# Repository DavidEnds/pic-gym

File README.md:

# pic-gym
A basic trainer for the PIC16F84A

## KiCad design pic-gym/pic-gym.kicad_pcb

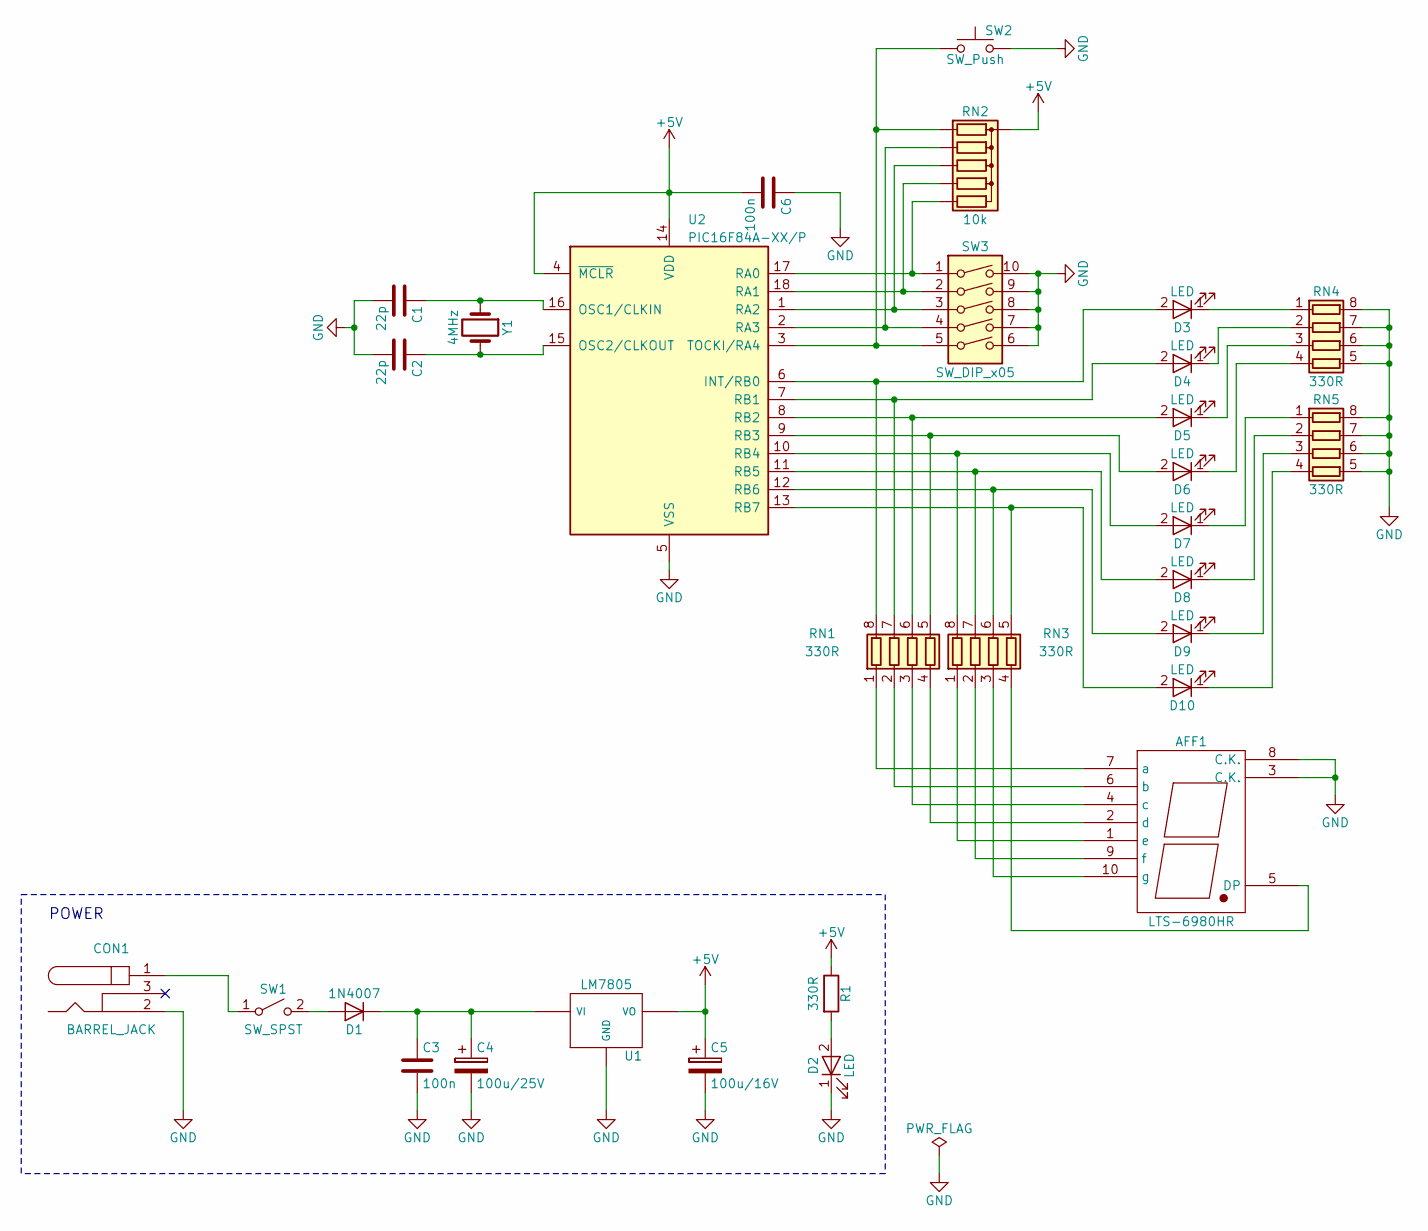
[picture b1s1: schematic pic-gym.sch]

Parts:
AFF1: LTS-6980HR; 7SegmentLED_LTS6760_LTS6780
C1, C2: 22p; C_0805_HandSoldering
C3, C6: 100n; C_0805_HandSoldering
C4: 100u/25V; C_Radial_D5_L11_P2
C5: 100u/16V; C_Radial_D5_L11_P2
CON1: BARREL_JACK; JACK_ALIM
D1: 1N4007; Diode_DO-35_SOD27_Horizontal_RM10
D2, D3, D4, D5, D6, D7, D8, D9, D10: LED; LED-3MM
R1: 330R; Resistor_Horizontal_RM10mm
RN1, RN3, RN4, RN5: 330R; R_Array_Concave_4x0603
RN2: 10k; Resistor_Array_SIP6
SW1: SW_SPST; SW_DIP_x1_Slide
SW2: SW_Push; SW_PUSH_6mm
SW3: SW_DIP_x05; SW_DIP_x5_Slide
U1: LM7805; TO-220_Neutral123_Vertical
U2: PIC16F84A-XX/P; DIP-18_W7.62mm_LongPads
Y1: 4MHz; HC-49V

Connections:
+5V: C5.1, C6.2, R1.1, RN2.1 (common), U1.3 (VO), U2.4 (~MCLR~), U2.14 (VDD)
GND: AFF1.3 (C.K.), AFF1.8 (C.K.), C1.2, C2.2, C3.2, C4.2, C5.2, C6.1, CON1.2, D2.1 (K), RN4.5 (R4.2), RN4.6 (R3.2), RN4.7 (R2.2), RN4.8 (R1.2), RN5.5 (R4.2), RN5.6 (R3.2), RN5.7 (R2.2), RN5.8 (R1.2), SW2.2, SW3.6, SW3.7, SW3.8, SW3.9, SW3.10, U1.2 (GND), U2.5 (VSS)
unnamed: AFF1.1 (e), RN3.1 (R1.1)
unnamed: AFF1.2 (d), RN1.4 (R4.1)
unnamed: AFF1.4 (c), RN1.3 (R3.1)
unnamed: AFF1.5 (DP), RN3.4 (R4.1)
unnamed: AFF1.6 (b), RN1.2 (R2.1)
unnamed: AFF1.7 (a), RN1.1 (R1.1)
unnamed: AFF1.9 (f), RN3.2 (R2.1)
unnamed: AFF1.10 (g), RN3.3 (R3.1)
unnamed: C1.1, U2.16 (OSC1/CLKIN), Y1.1
unnamed: C2.1, U2.15 (OSC2/CLKOUT), Y1.2
unnamed: C3.1, C4.1, D1.1 (K), U1.1 (VI)
unnamed: CON1.1, SW1.1 (A)
unnamed: D1.2 (A), SW1.2 (B)
unnamed: D2.2 (A), R1.2
unnamed: D3.1 (K), RN4.1 (R1.1)
unnamed: D3.2 (A), RN1.8 (R1.2), U2.6 (INT/RB0)
unnamed: D4.1 (K), RN4.2 (R2.1)
unnamed: D4.2 (A), RN1.7 (R2.2), U2.7 (RB1)
unnamed: D5.1 (K), RN4.3 (R3.1)
unnamed: D5.2 (A), RN1.6 (R3.2), U2.8 (RB2)
unnamed: D6.1 (K), RN4.4 (R4.1)
unnamed: D6.2 (A), RN1.5 (R4.2), U2.9 (RB3)
unnamed: D7.1 (K), RN5.1 (R1.1)
unnamed: D7.2 (A), RN3.8 (R1.2), U2.10 (RB4)
unnamed: D8.1 (K), RN5.2 (R2.1)
unnamed: D8.2 (A), RN3.7 (R2.2), U2.11 (RB5)
unnamed: D9.1 (K), RN5.3 (R3.1)
unnamed: D9.2 (A), RN3.6 (R3.2), U2.12 (RB6)
unnamed: D10.1 (K), RN5.4 (R4.1)
unnamed: D10.2 (A), RN3.5 (R4.2), U2.13 (RB7)
unnamed: RN2.2 (R1), SW2.1, SW3.5, U2.3 (TOCKI/RA4)
unnamed: RN2.3 (R2), SW3.4, U2.2 (RA3)
unnamed: RN2.4 (R3), SW3.3, U2.1 (RA2)
unnamed: RN2.5 (R4), SW3.2, U2.18 (RA1)
unnamed: RN2.6 (R5), SW3.1, U2.17 (RA0)

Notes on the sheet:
POWER

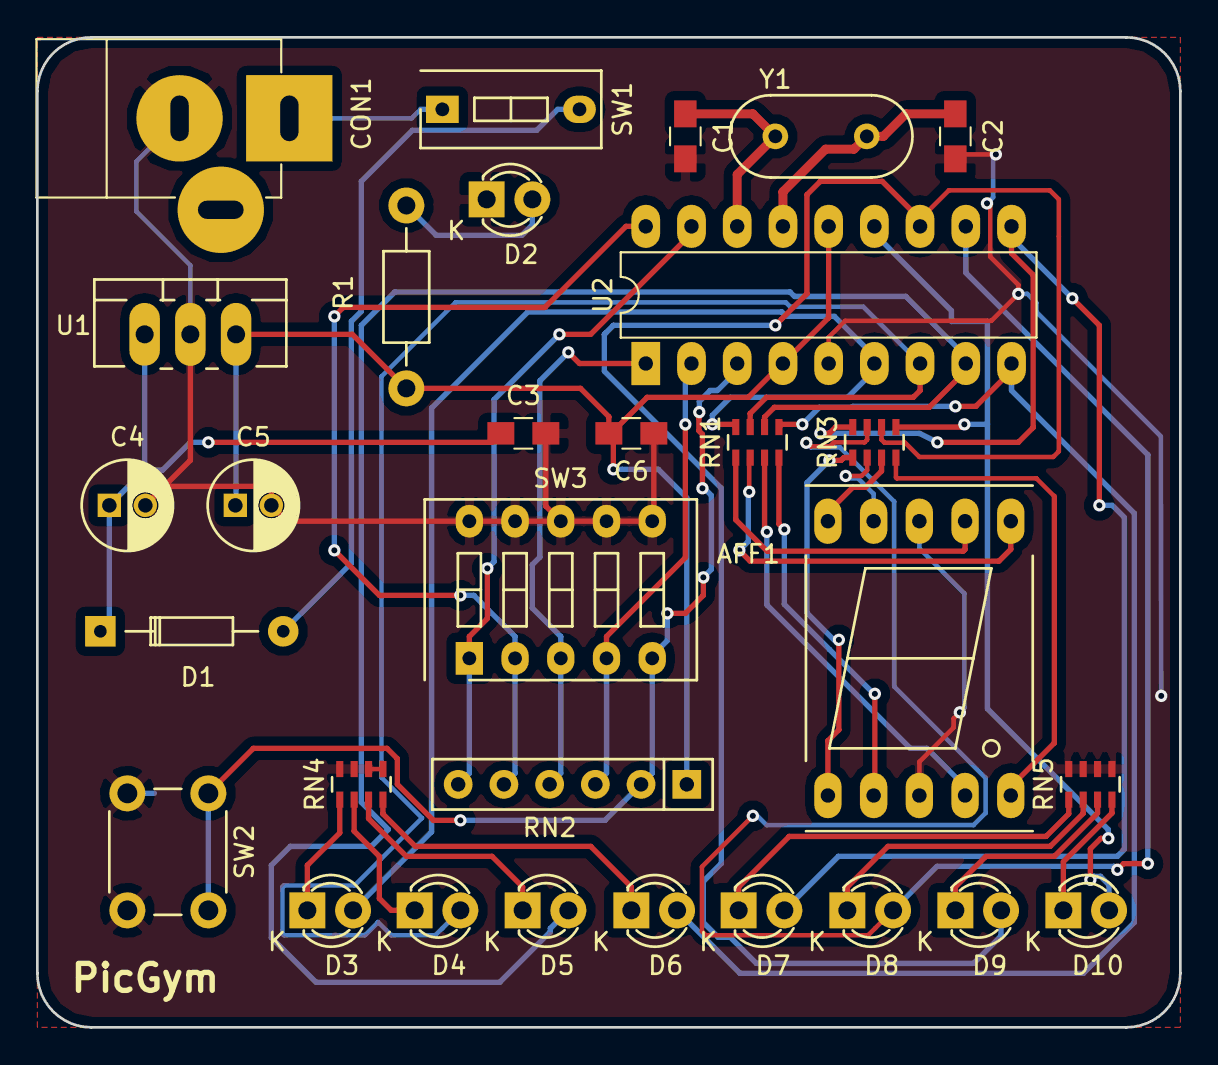
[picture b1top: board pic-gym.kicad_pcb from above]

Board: 2 copper layers, 63.5 x 55.0 mm, 30 parts (0 on the bottom side), 37 nets.

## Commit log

2017-01-22 Started PIC Gym project and added simple schematic and layout
2017-01-23 Finished schematic
2017-01-23 Netlist Exported
2017-01-23 Resistor arrays changed
2017-01-23 3D correct
2017-01-23 Layout in process
2017-01-30 Routed Board
2017-01-30 Silkscreen added
2017-01-30 Gerbers added
2017-03-05 Improving schematic
